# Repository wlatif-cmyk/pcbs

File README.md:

# pcbs

PCB design

e : walidahmadlatif@gmail.com

Soft robot controller

Haptic fitness watch

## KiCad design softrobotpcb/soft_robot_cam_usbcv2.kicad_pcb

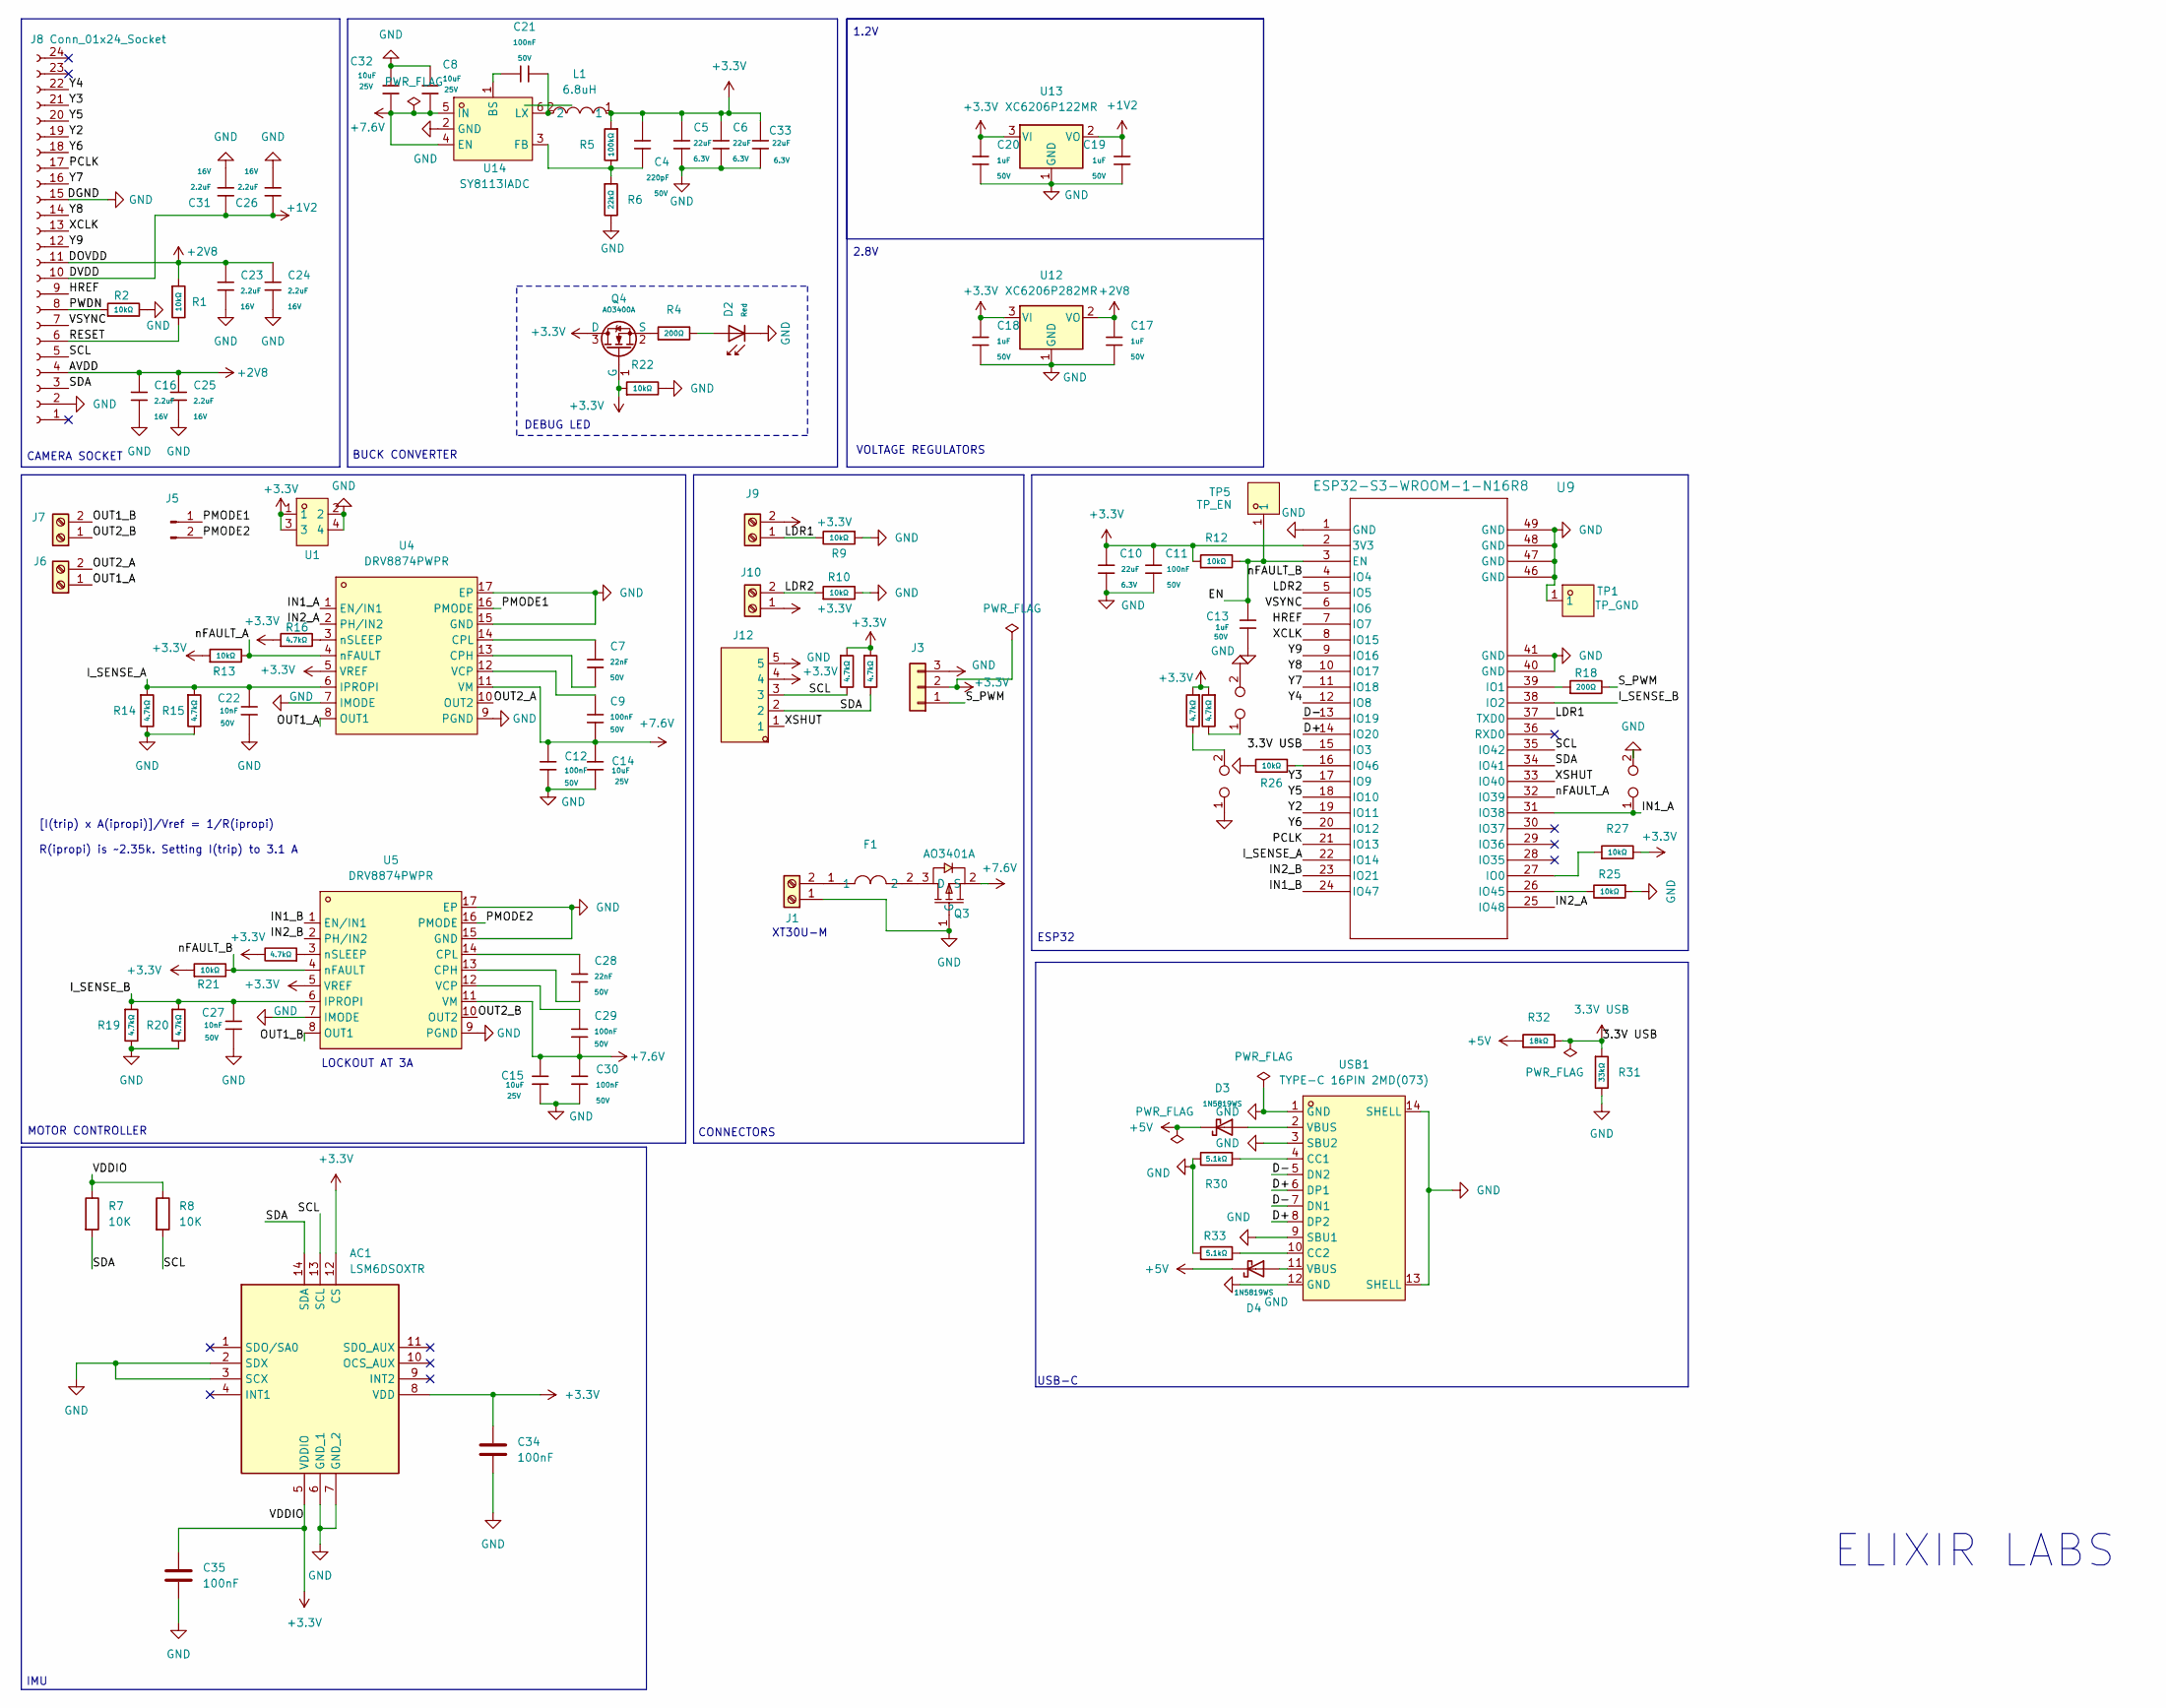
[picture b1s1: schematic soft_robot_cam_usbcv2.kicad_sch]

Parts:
AC1: LSM6DSOXTR; LGA-14L_L3.0-W2.5-P0.50-TL; Manufacturer_Part_Number LSM6DSOXTR; LCSC C481766
C4: 220pF; C_0402; Voltage Rated 50V; Tolerance ±10%; Part 0402B221K500NT; LCSC C1530
C5, C6, C10, C33: 22uF; C_0603; Voltage Rated 6.3V; Tolerance ±20%; Part CL10A226MQ8NRNC; LCSC C59461
C7, C28: 22nF; C_0603; Voltage Rated 50V; Tolerance ±10%; Part CL10B223KB8NNNC; LCSC C21122
C8, C14, C15, C32: 10uF; C_0603; Voltage Rated 25V; Tolerance ±20%; Part CL10A106MA8NRNC; LCSC C96446
C9, C11, C12, C21, C29, C30: 100nF; C_0603; Voltage Rated 50V; Tolerance ±10%; Part CC0603KRX7R9BB104; LCSC C14663
C13, C17, C18, C19, C20: 1uF; C_0603; Voltage Rated 50V; Tolerance ±10%; Part CL10A105KB8NNNC; LCSC C15849
C16, C23, C24, C25, C26, C31: 2.2uF; C_0603; Voltage Rated 16V; Tolerance ±10%; Part CL10A225KO8NNNC; LCSC C23630
C22, C27: 10nF; C_0603; Voltage Rated 50V; Tolerance ±10%; Part 0603B103K500NT; LCSC C57112
C34, C35: 100nF; C_0603
D2: Red; D_0603; Part KT-0603R; LCSC C2286
D3, D4: 1N5819WS; D_SOD-323; Forward Voltage (Vf@If) 600mV@1A; Reverse Voltage (Vr) 40V; Part 1N5819WS; LCSC C191023
F1: BHFUSE BSMD1206C-1700T; F1206; LCSC Part C41367230
J1: Connector; AMASS_XT30U-F_1x02_P5.0mm_Vertical; LCSC C99101
J3: Conn_01x03; JST_B3B-PH-K-S; LCSC C131339
J5: Conn_01x02_Pin; HDR-TH_2P-P1.27-V-M; LCSC C5243682
J6, J7, J9, J10: Screw_Terminal_01x02; JST_B2B-PH-K-S; LCSC C131337
J8: Conn_01x24_Socket; FPC-SMD_AFC07-S24ECA-00; LCSC C262643
J12: B5B-PH-K-S-(LF)(SN); CONN-TH_B5B-PH-K-S-LF-SN; LCSC Part C157993
L1: 6.8uH; IND-SMD_L6.0-W6.0; LCSC C341066
Q3: AO3401A; SOT-23_L2.9-W1.3-P1.90-LS2.4-BR; LCSC Part C15127
Q4: AO3400A; Q_SOT-23; Part AO3400A; LCSC C20917
R1, R2, R9, R10, R12, R13, R21, R22, R25, R26, R27: 10kΩ; R_0603; Overload Voltage (Max) 75V; Tolerance ±1%; Part 0603WAF1002T5E; LCSC C25804
R3, R11, R14, R15, R16, R17, R19, R20, R23, R24: 4.7kΩ; R_0603; Overload Voltage (Max) 75V; Tolerance ±1%; Part 0603WAF4701T5E; LCSC C23162
R4, R18: 200Ω; R_0402; Overload Voltage (Max) 50V; Tolerance ±1%; Part 0402WGF2000TCE; LCSC C25087
R5: 100kΩ; R_0402; Overload Voltage (Max) 50V; Tolerance ±1%; Part 0402WGF1003TCE; LCSC C25741
R6: 22kΩ; R_0402; Overload Voltage (Max) 50V; Tolerance ±1%; Part 0402WGF2202TCE; LCSC C25768
R7, R8: 10K; R_0603
R30, R33: 5.1kΩ; R_0603; Overload Voltage (Max) 75V; Tolerance ±1%; Part 0603WAF5101T5E; LCSC C23186
R31: 33kΩ; R_0603; Overload Voltage (Max) 75V; Tolerance ±1%; Part 0603WAF3302T5E; LCSC C4216
R32: 18kΩ; R_0603; Overload Voltage (Max) 75V; Tolerance ±1%; Part 0603WAF1802T5E; LCSC C25810
TP1: TP_GND; CONN-SMD_L3.2-1.6; LCSC Part C159866
TP2, TP3, TP4: TestPoint_2Pole; TestPoint_2Pads_Pitch2.54mm_Drill0.8mm
TP5: TP_EN; CONN-SMD_L3.2-1.6; LCSC Part C159866
U1: PZ127-2-02-Z; HDR-TH_4P-P1.27-V-M-R2-C2-S1.27_MH127V-12-04-0820; LCSC Part C5372806
U4, U5: DRV8874PWPR; HTSSOP-16_L5.0-W4.4-P0.65-LS6.4-BL-EP; LCSC Part C1855818
U9: ESP32-S3-WROOM-1-N16R8; ESP32-S3-WROOM-1_EXP; LCSC C2913202
U12: XC6206P282MR; SOT-23-3; LCSC C14255
U13: XC6206P122MR; SOT-23-3; LCSC C2827649
U14: SY8113IADC; TSOT-23-6_L2.9-W1.6-P0.95-LS2.8-BL; LCSC C479075
USB1: TYPE-C 16PIN 2MD(073); USB-C-SMD_TYPE-C-6PIN-2MD-073; LCSC Part C2765186

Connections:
+1V2: C19.1, C26.1, C31.1, J8.10, U13.2 (VO)
+2V8: C16.1, C17.1, C23.1, C24.1, C25.1, J8.4, J8.11, R1.1, U12.2 (VO)
+5V: D3.1, D4.1, R32.1
+7.6V: C8.2, C9.2, C12.1, C14.1, C15.1, C29.2, C30.1, C32.2, Q3.2 (S), U4.11 (VM), U5.11 (VM), U14.4 (EN), U14.5 (IN)
/BOOT: R27.1, U9.27 (IO0)
/D+: U9.14 (IO20), USB1.6 (DP1), USB1.8 (DP2)
/D-: U9.13 (IO19), USB1.5 (DN2), USB1.7 (DN1)
/EN: C13.1, R12.2, TP5.1, U9.3 (EN)
/HREF: J8.9, U9.7 (IO7)
/IN1_A: TP2.1, U4.1 (EN/IN1), U9.31 (IO38)
/IN1_B: U5.1 (EN/IN1), U9.24 (IO47)
/IN2_A: U4.2 (PH/IN2), U9.25 (IO48)
/IN2_B: U5.2 (PH/IN2), U9.23 (IO21)
/I_SENSE_A: C22.2, R14.1, R15.1, U4.6 (IPROPI), U9.22 (IO14)
/I_SENSE_B: C27.2, R19.1, R20.1, U5.6 (IPROPI), U9.38 (IO2)
/LDR1: J9.1, R9.2, U9.37 (TXD0)
/LDR2: J10.2, R10.1, U9.5 (IO5)
/OUT1_A: J6.1, U4.8 (OUT1)
/OUT1_B: J7.2, U5.8 (OUT1)
/OUT2_A: J6.2, U4.10 (OUT2)
/OUT2_B: J7.1, U5.10 (OUT2)
/PCLK: J8.17, U9.21 (IO13)
/PMODE1: J5.1, U4.16 (PMODE)
/PMODE2: J5.2, U5.16 (PMODE)
/PWDN: J8.8, R2.1
/RESET: J8.6, R1.2
/SCL: AC1.13 (SCL), J8.5, J12.3, R8.2, R11.2, U9.35 (IO42)
/SDA: AC1.14 (SDA), J8.3, J12.2, R7.2, R23.2, U9.34 (IO41)
/S_PWM: J3.1, R18.2
/VSYNC: J8.7, U9.6 (IO6)
/XCLK: J8.13, U9.8 (IO15)
/XSHUT: J12.1, U9.33 (IO40)
/Y2: J8.19, U9.19 (IO11)
/Y3: J8.21, U9.17 (IO9)
/Y4: J8.22, U9.12 (IO8)
/Y5: J8.20, U9.18 (IO10)
/Y6: J8.18, U9.20 (IO12)
/Y7: J8.16, U9.11 (IO18)
/Y8: J8.14, U9.10 (IO17)
/Y9: J8.12, U9.9 (IO16)
/nFAULT_A: R13.2, U4.4 (nFAULT), U9.32 (IO39)
/nFAULT_B: R21.2, U5.4 (nFAULT), U9.4 (IO4)
unnamed: D2.2, R4.2
unnamed: D3.2, USB1.2 (VBUS)
unnamed: D4.2, USB1.11 (VBUS)
unnamed: F1.1, J1.2
unnamed: F1.2, Q3.3 (D)
unnamed: Q4.2 (S), R4.1
unnamed: R3.2, TP3.2
unnamed: R24.2, TP4.1
unnamed: C7.2, U4.13 (CPH)
unnamed: C7.1, U4.14 (CPL)
unnamed: C9.1, U4.12 (VCP)
unnamed: R16.2, U4.3 (nSLEEP)
unnamed: C28.2, U5.13 (CPH)
unnamed: C28.1, U5.14 (CPL)
unnamed: C29.1, U5.12 (VCP)
unnamed: R17.1, U5.3 (nSLEEP)
unnamed: R18.1, U9.39 (IO1)
unnamed: R25.2, U9.26 (IO45)
unnamed: R26.2, U9.16 (IO46)
unnamed: C21.1, U14.1 (BS)
unnamed: C4.2, R5.2, R6.1, U14.3 (FB)
unnamed: C21.2, L1.2, U14.6 (LX)
unnamed: R30.1, USB1.4 (CC1)
unnamed: R33.2, USB1.10 (CC2)

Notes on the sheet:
USB-C
ESP32
XT30U-M
DEBUG LED
1.2V
MOTOR CONTROLLER
2.8V
CAMERA SOCKET
BUCK CONVERTER
CONNECTORS
ELIXIR LABS
VOLTAGE REGULATORS
IMU
[I(trip) x A(ipropi)]/Vref = 1/R(ipropi) R(ipropi) is ~2.35k. Setting I(trip) to 3.1 A
LOCKOUT AT 3A

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
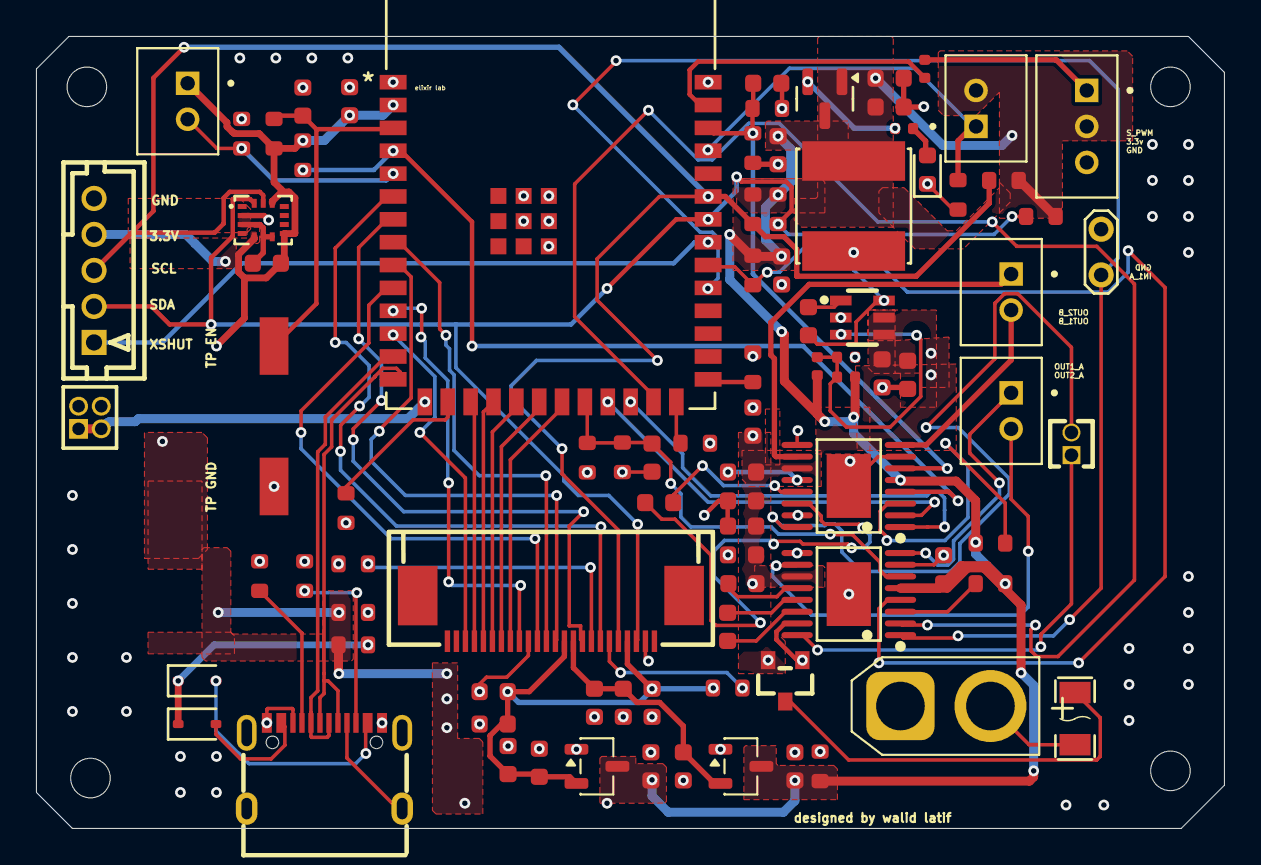
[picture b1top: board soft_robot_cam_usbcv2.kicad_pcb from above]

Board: 4 copper layers, 66.0 x 44.0 mm, 89 parts (0 on the bottom side), 66 nets.

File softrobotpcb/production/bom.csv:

Designator,Footprint,Quantity,Value,LCSC Part #
AC1,LGA-14L_L3.0-W2.5-P0.50-TL,1,LSM6DSOXTR,
"C10, C33, C5, C6",C_0603,4,22uF,C59461
"C11, C12, C21, C29, C30, C9",C_0603,6,100nF,C14663
"C13, C17, C18, C19, C20",C_0603,5,1uF,C15849
"C14, C15, C32, C8",C_0603,4,10uF,C96446
"C16, C23, C24, C25, C26, C31",C_0603,6,2.2uF,C23630
"C22, C27",C_0603,2,10nF,C57112
"C28, C7",C_0603,2,22nF,C21122
"C34, C35",C_0603,2,100nF,
C4,C_0402,1,220pF,C1530
D2,D_0603,1,Red,C2286
"D3, D4",D_SOD-323,2,1N5819WS,C191023
F1,F1206,1,BHFUSE BSMD1206C-1700T,C41367230
J1,AMASS_XT30U-F_1x02_P5.0mm_Vertical,1,Connector,C99101
"J10, J6, J7, J9",JST_B2B-PH-K-S,4,Screw_Terminal_01x02,C131337
J12,CONN-TH_B5B-PH-K-S-LF-SN,1,B5B-PH-K-S-(LF)(SN),C157993
J3,JST_B3B-PH-K-S,1,Conn_01x03,C131339
J5,HDR-TH_2P-P1.27-V-M,1,Conn_01x02_Pin,C5243682
J8,FPC-SMD_AFC07-S24ECA-00,1,Conn_01x24_Socket,C262643
L1,IND-SMD_L6.0-W6.0,1,6.8uH,C341066
Q3,SOT-23_L2.9-W1.3-P1.90-LS2.4-BR,1,AO3401A,C15127
Q4,Q_SOT-23,1,AO3400A,C20917
"R1, R10, R12, R13, R2, R21, R22, R25, R26, R9",R_0603,10,10kΩ,C25804
"R11, R14, R15, R16, R17, R19, R20, R23, R24, R3",R_0603,10,4.7kΩ,C23162
"R18, R4",R_0402,2,200Ω,C25087
"R27, R30, R33",R_0603,3,5.1kΩ,C23186
R31,R_0603,1,33kΩ,C4216
R32,R_0603,1,18kΩ,C25810
R5,R_0402,1,100kΩ,C25741
R6,R_0402,1,22kΩ,C25768
"R7, R8",R_0603,2,10K,
TP1,CONN-SMD_L3.2-1.6,1,TP_GND,C159866
"TP2, TP3, TP4",TestPoint_2Pads_Pitch2.54mm_Drill0.8mm,3,TestPoint_2Pole,
TP5,CONN-SMD_L3.2-1.6,1,TP_EN,C159866
U1,HDR-TH_4P-P1.27-V-M-R2-C2-S1.27_MH127V-12-04-0820,1,PZ127-2-02-Z,C5372806
U12,SOT-23-3,1,XC6206P282MR,C14255
U13,SOT-23-3,1,XC6206P122MR,C2827649
U14,TSOT-23-6_L2.9-W1.6-P0.95-LS2.8-BL,1,SY8113IADC,C479075 
"U4, U5",HTSSOP-16_L5.0-W4.4-P0.65-LS6.4-BL-EP,2,DRV8874PWPR,C1855818
U9,ESP32-S3-WROOM-1_EXP,1,ESP32-S3-WROOM-1-N16R8,C2913202
USB1,USB-C-SMD_TYPE-C-6PIN-2MD-073,1,TYPE-C 16PIN 2MD(073),C2765186

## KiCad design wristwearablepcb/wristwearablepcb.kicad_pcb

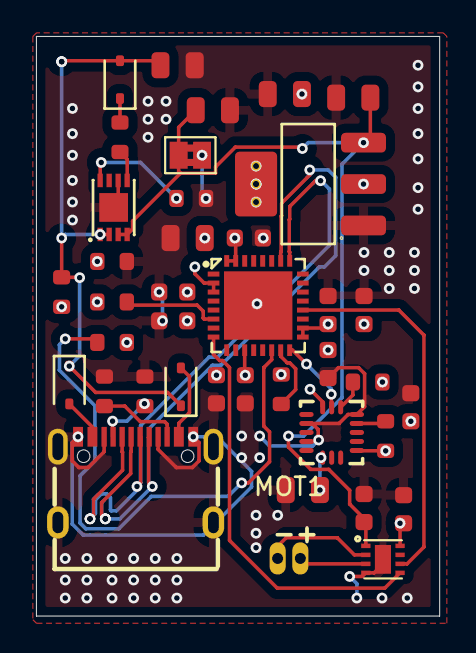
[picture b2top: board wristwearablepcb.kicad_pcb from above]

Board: 4 copper layers, 22.4 x 32.2 mm, 39 parts (0 on the bottom side), 23 nets.

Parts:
BT1: Battery; SolderJumper-2_P1.3mm_Bridged2Bar_Pad1.0x1.5mm
C1, C11, C12: 10uF; C_0805
C2: 22uF; C_0805
C3, C8, C9, C13: 100nF; C_0603
C4, C5, C6, C10: 1uF; C_0603
C7: 10nF; C_0603
C14, C15: 4.7uF; C_0805
C16, C17: 0.1uF; C_0603
D1, D2, D3: 1N5819WS; D_SOD-323
MOT1: LCM1027A2445F; VIBRATING-MOTOR-SMD_WELDING
R1, R2: 5.1k; R_0603
R3: 18kΩ; R_0603
R4: 33kΩ; R_0603
R7, R8, R11: 10k; R_0603
R9: 2k; R_0603
R10: 470; R_0603
R_SCL1: 10k; R_0603
R_SDA1: 10k; R_0603
U1: AMS1117; SOT-223-3_L6.5-W3.4-P2.30-LS7.0-BR
U2: LIS3DHTR_C15134; LGA-16_L3.0-W3.0-P0.50-TL
U3: ESP32-C3; QFN-32_L5.0-W5.0-P0.50-TL-EP3.7
U4: MCP73831-2ACI/MC; TDFN-8_L3.0-W2.0-P0.50-BL-EP1.6
U5: DRV8837DSGR; WSON-8_L2.0-W2.0-P0.50-TL-EP
USB1: TYPE-C 16PIN 2MD(073); USB-C-SMD_TYPE-C-6PIN-2MD-073

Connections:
+3.3V: C2.1, C3.1, C4.1, C5.1, C6.1, C7.1, C8.1, C9.1, C10.1, C11.1, C12.2, C13.2, C17.1, R3.2, R4.1, R7.1, R8.2, R11.2, R_SCL1.1, R_SDA1.1, U1.2 (VOUT), U1.4 (VOUT), U2.1 (VDD_IO), U2.8 (CS), U2.14 (VDD), U3.2 (VDD3P3), U3.3 (VDD3P3), U3.11 (VDD3P3_RTC), U3.17 (VDD3P3_CPU), U3.18 (VDD_SPI), U3.31 (VDDA), U3.32 (VDDA), U5.8 (VCC)
+5V: C14.1, D1.1, D2.1, D3.2, R3.1, U4.1 (VDD), U4.2 (VDD)
/3.7V LiPo: BT1.1 (+), C1.1, C15.1, C16.1, U1.3 (VIN), U4.3 (VBAT), U4.4 (VBAT), U5.1 (VM)
/D+: U3.26 (GPIO19), USB1.6 (DP1), USB1.8 (DP2)
/D-: U3.25 (GPIO18), USB1.5 (DN2), USB1.7 (DN1)
/IN1: U3.20 (SPIWP), U5.6 (IN1)
/IN2: U3.8 (GPIO3), U5.5 (IN2)
/SCL: R_SCL1.2, U2.4 (SCL/SPC)
/SDA: R_SDA1.2, U2.6 (SDA/SDI/SDO)
/SDO: U2.7 (SDO/SA0), U3.16 (GPIO10)
GND: BT1.2 (-), C1.2, C2.2, C3.2, C4.2, C5.2, C6.2, C7.2, C8.2, C9.2, C10.2, C11.2, C12.1, C13.1, C14.2, C15.2, C16.2, C17.2, R1.1, R2.1, R4.2, R9.2, U1.1 (GND), U2.5 (GND), U2.10 (RES), U2.12 (GND), U3.33 (EP), U4.6 (VSS), U4.9 (EP), U5.4 (GND), U5.9 (EP), USB1.1 (GND), USB1.3 (SBU2), USB1.9 (SBU1), USB1.12 (GND), USB1.13 (SHELL), USB1.14 (SHELL)
unnamed: D1.2, USB1.2 (VBUS)
unnamed: D2.2, USB1.11 (VBUS)
unnamed: D3.1, R10.1
unnamed: MOT1.2 (+), U5.3 (OUT2)
unnamed: MOT1.1 (-), U5.2 (OUT1)
unnamed: R7.2, U3.6 (GPIO2)
unnamed: R8.1, U3.14 (GPIO8)
unnamed: R11.1, U3.15 (GPIO9)
unnamed: R9.1, U4.8 (PROG)
unnamed: R10.2, U4.5 (STAT)
unnamed: R1.2, USB1.4 (CC1)
unnamed: R2.2, USB1.10 (CC2)

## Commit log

2026-02-11 Added haptic/accelerometer wrist gadget
2026-02-11 changed images
2026-02-11 changing an image
2026-02-12 updated sche and pcb
2026-02-13 added softrobot
2026-02-14 added naming to important pcb components/pins
2026-02-14 swapped out some images
2026-02-18 completely replaced pcb for softrobot
2026-02-18 deleted random folder
2026-03-02 big updates!!!!
2026-03-03 added .step files for conversion
